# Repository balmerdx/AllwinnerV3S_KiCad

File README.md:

# Balmer Allwinner V3S KICAD scematic & pcb

Allwinner V3S - это пожалуй один из наиболее дешёвых system on chip для embedded linux.

Перечислю его ключевые особенности.
* встроенные 64 мегабайта DRAM
* RGB интерфейс для подключения дисплея
* встроенный PNY для Ethernet 100 Mbit
* USB 2.0 OTG
* встроенный DAC и усилитель для наушников

Это позволяет сделать достаточно дешёвый одноплатник.

Обратите внимание!!!! Плата разведена для Step-Down на EA3036. Микросхема EA3036C имеет несколько другой pinout. К сожалению мне прислали EA3036C, и поэтому на плате есть некрасивое место с её вкорячиванием.

Плата разведена под дисплей с 800x480 с capacitive touch (G05012AG02A1, G050AGZ085A1).

То-же, самое но с корпусом.

### Сравним с Lichee PI

По размеру мой вариант несколько больше. Но за счёт расположенных разъёмов конечный вариант будет явно компактнее. Разводка Lichee PI мне нравится как пример максимально плотного монтажа. Для отладки это нормально. Но в реальной жизни непонятно, что делать с этими случайным образом раскиданными разъёмами.

### Информация
* [Схема в pdf формате](info/balmer_allwinner_v3s_v2.pdf)
* [Информация, как собирать linux](info/Buildroot_AllwinnerV3S.pdf)

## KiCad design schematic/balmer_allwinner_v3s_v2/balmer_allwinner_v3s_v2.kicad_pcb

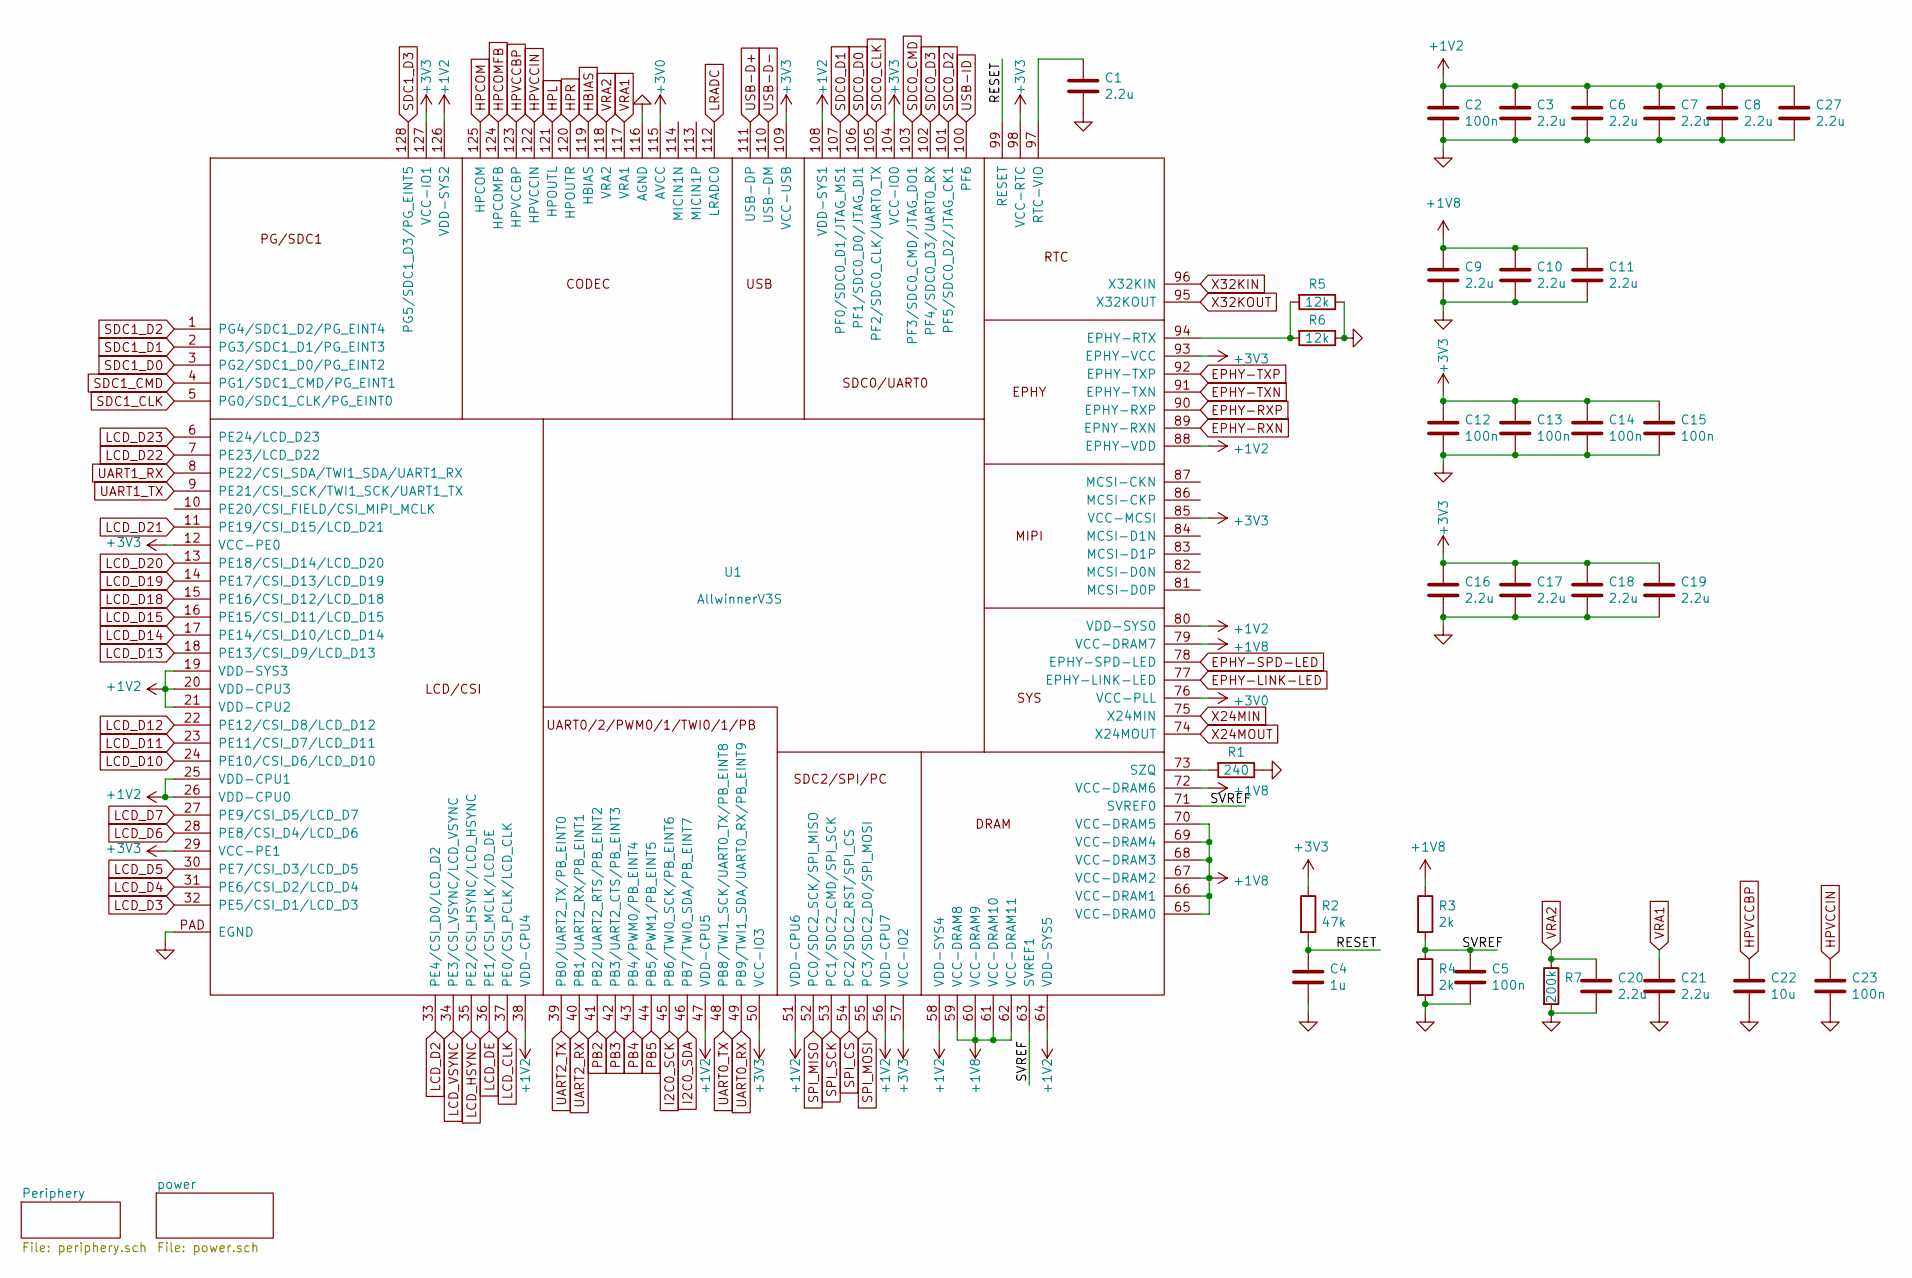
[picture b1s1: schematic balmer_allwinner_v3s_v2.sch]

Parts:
C1, C3, C6, C7, C8, C9, C10, C11, C16, C17, C18, C19, C20, C21, C27: 2.2u; C_0805_2012Metric
C2, C5, C12, C13, C14, C15, C23: 100n; C_0603_1608Metric
C4: 1u; C_0603_1608Metric
C22: 10u; C_0805_2012Metric
R1: 240; R_0603_1608Metric
R2: 47k; R_0603_1608Metric
R3, R4: 2k; R_0603_1608Metric
R5, R6: 12k; R_0603_1608Metric
R7: 200k; R_0603_1608Metric
U1: AllwinnerV3S; eLQFP-128_14x14mm_P0.4mm

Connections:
+1V2: C2.1, C3.1, C6.1, C7.1, C8.1, C27.1, U1.19 (VDD-SYS3), U1.20 (VDD-CPU3), U1.21 (VDD-CPU2), U1.25 (VDD-CPU1), U1.26 (VDD-CPU0), U1.38 (VDD-CPU4), U1.47 (VDD-CPU5), U1.51 (VDD-CPU6), U1.56 (VDD-CPU7), U1.58 (VDD-SYS4), U1.64 (VDD-SYS5), U1.80 (VDD-SYS0), U1.88 (EPHY-VDD), U1.108 (VDD-SYS1), U1.126 (VDD-SYS2); also elsewhere on the board
+1V8: C9.1, C10.1, C11.1, R3.1, U1.59 (VCC-DRAM8), U1.60 (VCC-DRAM9), U1.61 (VCC-DRAM10), U1.62 (VCC-DRAM11), U1.65 (VCC-DRAM0), U1.66 (VCC-DRAM1), U1.67 (VCC-DRAM2), U1.68 (VCC-DRAM3), U1.69 (VCC-DRAM4), U1.70 (VCC-DRAM5), U1.72 (VCC-DRAM6), U1.79 (VCC-DRAM7); also elsewhere on the board
+3V0: U1.76 (VCC-PLL), U1.115 (AVCC); also elsewhere on the board
+3V3: C12.1, C13.1, C14.1, C15.1, C16.1, C17.1, C18.1, C19.1, R2.1, U1.12 (VCC-PE0), U1.29 (VCC-PE1), U1.50 (VCC-IO3), U1.57 (VCC-IO2), U1.85 (VCC-MCSI), U1.93 (EPHY-VCC), U1.98 (VCC-RTC), U1.104 (VCC-IO0), U1.109 (VCC-USB), U1.127 (VCC-IO1); also elsewhere on the board
/RESET: C4.1, R2.2, U1.99 (RESET)
/SVREF: C5.1, R3.2, R4.1, U1.63 (SVREF1), U1.71 (SVREF0)
EPHY-LINK-LED: U1.77 (EPHY-LINK-LED); also elsewhere on the board
EPHY-RXN: U1.89 (EPNY-RXN); also elsewhere on the board
EPHY-RXP: U1.90 (EPHY-RXP); also elsewhere on the board
EPHY-SPD-LED: U1.78 (EPHY-SPD-LED); also elsewhere on the board
EPHY-TXN: U1.91 (EPHY-TXN); also elsewhere on the board
EPHY-TXP: U1.92 (EPHY-TXP); also elsewhere on the board
GND: C1.2, C2.2, C3.2, C4.2, C5.2, C6.2, C7.2, C8.2, C9.2, C10.2, C11.2, C12.2, C13.2, C14.2, C15.2, C16.2, C17.2, C18.2, C19.2, C20.2, C21.2, C22.2, C23.2, C27.2, R1.1, R4.2, R5.1, R6.1, R7.2, U1.116 (AGND), U1.PAD (EGND); also elsewhere on the board
HBIAS: U1.119 (HBIAS); also elsewhere on the board
HPCOM: U1.125 (HPCOM); also elsewhere on the board
HPCOMFB: U1.124 (HPCOMFB); also elsewhere on the board
HPL: U1.121 (HPOUTL); also elsewhere on the board
HPR: U1.120 (HPOUTR); also elsewhere on the board
HPVCCBP: C22.1, U1.123 (HPVCCBP)
HPVCCIN: C23.1, U1.122 (HPVCCIN)
I2C0_SCK: U1.45 (PB6/TWI0_SCK/PB_EINT6); also elsewhere on the board
I2C0_SDA: U1.46 (PB7/TWI0_SDA/PB_EINT7); also elsewhere on the board
LCD_CLK: U1.37 (PE0/CSI_PCLK/LCD_CLK); also elsewhere on the board
LCD_D2: U1.33 (PE4/CSI_D0/LCD_D2); also elsewhere on the board
LCD_D3: U1.32 (PE5/CSI_D1/LCD_D3); also elsewhere on the board
LCD_D4: U1.31 (PE6/CSI_D2/LCD_D4); also elsewhere on the board
LCD_D5: U1.30 (PE7/CSI_D3/LCD_D5); also elsewhere on the board
LCD_D6: U1.28 (PE8/CSI_D4/LCD_D6); also elsewhere on the board
LCD_D7: U1.27 (PE9/CSI_D5/LCD_D7); also elsewhere on the board
LCD_D10: U1.24 (PE10/CSI_D6/LCD_D10); also elsewhere on the board
LCD_D11: U1.23 (PE11/CSI_D7/LCD_D11); also elsewhere on the board
LCD_D12: U1.22 (PE12/CSI_D8/LCD_D12); also elsewhere on the board
LCD_D13: U1.18 (PE13/CSI_D9/LCD_D13); also elsewhere on the board
LCD_D14: U1.17 (PE14/CSI_D10/LCD_D14); also elsewhere on the board
LCD_D15: U1.16 (PE15/CSI_D11/LCD_D15); also elsewhere on the board
LCD_D18: U1.15 (PE16/CSI_D12/LCD_D18); also elsewhere on the board
LCD_D19: U1.14 (PE17/CSI_D13/LCD_D19); also elsewhere on the board
LCD_D20: U1.13 (PE18/CSI_D14/LCD_D20); also elsewhere on the board
LCD_D21: U1.11 (PE19/CSI_D15/LCD_D21); also elsewhere on the board
LCD_D22: U1.7 (PE23/LCD_D22); also elsewhere on the board
LCD_D23: U1.6 (PE24/LCD_D23); also elsewhere on the board
LCD_DE: U1.36 (PE1/CSI_MCLK/LCD_DE); also elsewhere on the board
LCD_HSYNC: U1.35 (PE2/CSI_HSYNC/LCD_HSYNC); also elsewhere on the board
LCD_VSYNC: U1.34 (PE3/CSI_VSYNC/LCD_VSYNC); also elsewhere on the board
LRADC: U1.112 (LRADC0); also elsewhere on the board
unnamed: C1.1, U1.97 (RTC-VIO)
unnamed: R1.2, U1.73 (SZQ)
unnamed: R5.2, R6.2, U1.94 (EPHY-RTX)
PB2: U1.41 (PB2/UART2_RTS/PB_EINT2); also elsewhere on the board
PB3: U1.42 (PB3/UART2_CTS/PB_EINT3); also elsewhere on the board
PB4: U1.43 (PB4/PWM0/PB_EINT4); also elsewhere on the board
PB5: U1.44 (PB5/PWM1/PB_EINT5); also elsewhere on the board
SDC0_CLK: U1.105 (PF2/SDC0_CLK/UART0_TX); also elsewhere on the board
SDC0_CMD: U1.103 (PF3/SDC0_CMD/JTAG_DO1); also elsewhere on the board
SDC0_D0: U1.106 (PF1/SDC0_D0/JTAG_DI1); also elsewhere on the board
SDC0_D1: U1.107 (PF0/SDC0_D1/JTAG_MS1); also elsewhere on the board
SDC0_D2: U1.101 (PF5/SDC0_D2/JTAG_CK1); also elsewhere on the board
SDC0_D3: U1.102 (PF4/SDC0_D3/UART0_RX); also elsewhere on the board
SDC1_CLK: U1.5 (PG0/SDC1_CLK/PG_EINT0); also elsewhere on the board
SDC1_CMD: U1.4 (PG1/SDC1_CMD/PG_EINT1); also elsewhere on the board
SDC1_D0: U1.3 (PG2/SDC1_D0/PG_EINT2); also elsewhere on the board
SDC1_D1: U1.2 (PG3/SDC1_D1/PG_EINT3); also elsewhere on the board
SDC1_D2: U1.1 (PG4/SDC1_D2/PG_EINT4); also elsewhere on the board
SDC1_D3: U1.128 (PG5/SDC1_D3/PG_EINT5); also elsewhere on the board
SPI_CS: U1.54 (PC2/SDC2_RST/SPI_CS); also elsewhere on the board
SPI_MISO: U1.52 (PC0/SDC2_SCK/SPI_MISO); also elsewhere on the board
SPI_MOSI: U1.55 (PC3/SDC2_D0/SPI_MOSI); also elsewhere on the board
SPI_SCK: U1.53 (PC1/SDC2_CMD/SPI_SCK); also elsewhere on the board
UART0_RX: U1.49 (PB9/TWI1_SDA/UART0_RX/PB_EINT9); also elsewhere on the board
UART0_TX: U1.48 (PB8/TWI1_SCK/UART0_TX/PB_EINT8); also elsewhere on the board
UART1_RX: U1.8 (PE22/CSI_SDA/TWI1_SDA/UART1_RX); also elsewhere on the board
UART1_TX: U1.9 (PE21/CSI_SCK/TWI1_SCK/UART1_TX); also elsewhere on the board
UART2_RX: U1.40 (PB1/UART2_RX/PB_EINT1); also elsewhere on the board
UART2_TX: U1.39 (PB0/UART2_TX/PB_EINT0); also elsewhere on the board
USB-D+: U1.111 (USB-DP); also elsewhere on the board
USB-D-: U1.110 (USB-DM); also elsewhere on the board
USB-ID: U1.100 (PF6); also elsewhere on the board
VRA1: C21.1, U1.117 (VRA1)
VRA2: C20.1, R7.1, U1.118 (VRA2)
X24MIN: U1.75 (X24MIN); also elsewhere on the board
X24MOUT: U1.74 (X24MOUT); also elsewhere on the board
X32KIN: U1.96 (X32KIN); also elsewhere on the board
X32KOUT: U1.95 (X32KOUT); also elsewhere on the board

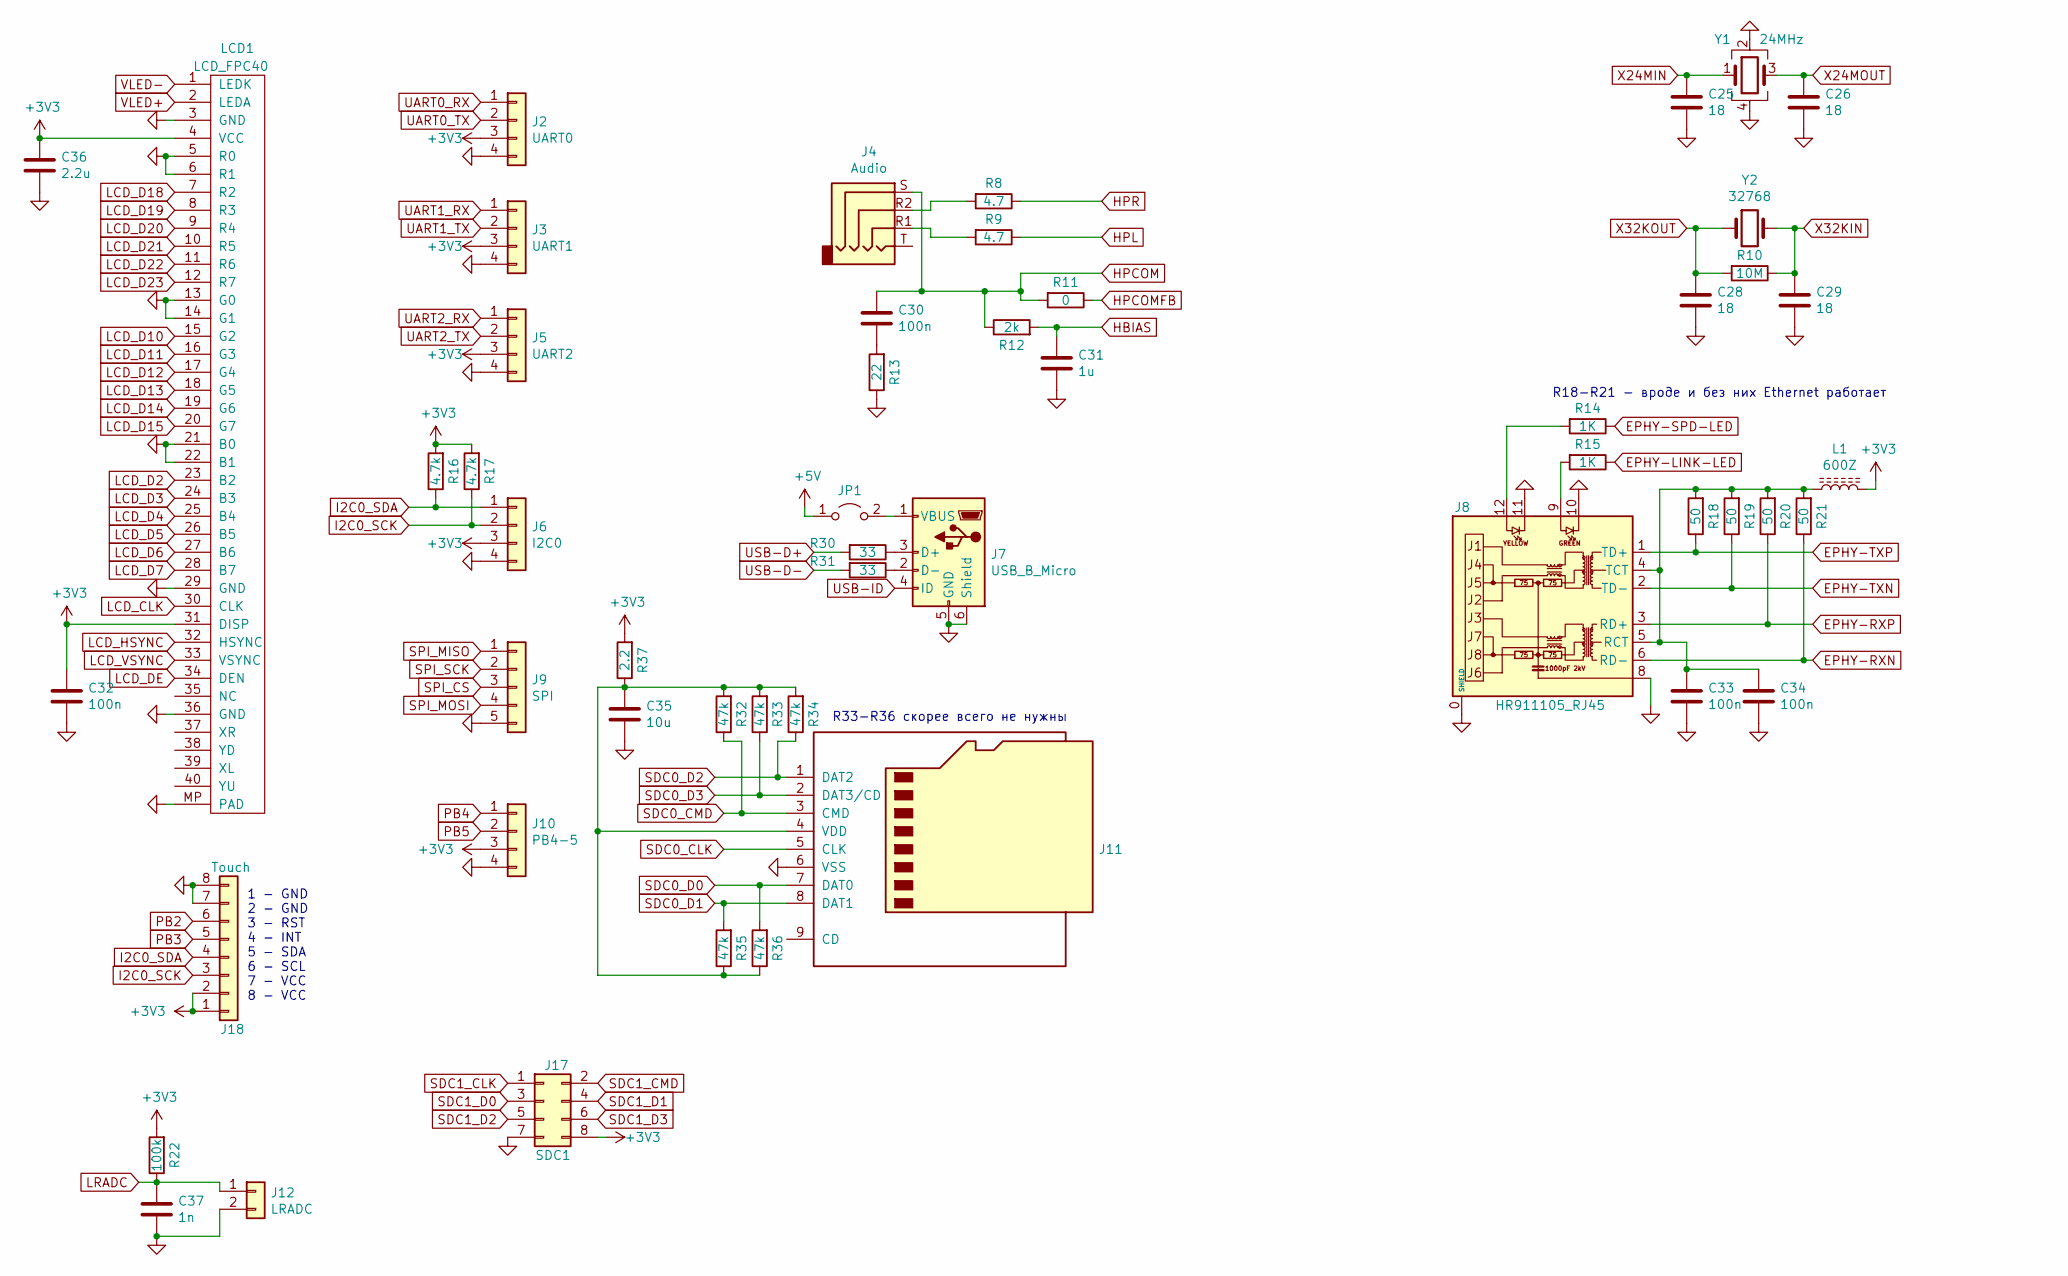
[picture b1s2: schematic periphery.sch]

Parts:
C25, C26, C28, C29: 18; C_0603_1608Metric
C30, C32, C33, C34: 100n; C_0603_1608Metric
C31: 1u; C_0603_1608Metric
C35: 10u; C_1206_3216Metric
C36: 2.2u; C_0805_2012Metric
C37: 1n; C_0603_1608Metric
J2: UART0; PinSocket_1x04_P1.27mm_Vertical
J3: UART1; PinSocket_1x04_P1.27mm_Vertical
J4: Audio; Jack_3.5mm_PJ320D_Horizontal
J5: UART2; PinSocket_1x04_P1.27mm_Vertical
J6: I2C0; PinSocket_1x04_P1.27mm_Vertical
J7: USB_B_Micro; USB_Micro-B_Molex-105017-0001
J8: HR911105_RJ45
J9: SPI; PinSocket_1x05_P1.27mm_Vertical
J10: PB4-5; PinSocket_1x04_P1.27mm_Vertical
J11: Micro_SD_Card_Ebay; Conn_uSDcard
J12: LRADC; PinSocket_1x02_P1.27mm_Vertical
J17: SDC1; PinHeader_2x04_P2.54mm_Vertical
J18: Touch; Hirose_FH12-8S-0.5SH_1x08-1MP_P0.50mm_Horizontal
JP1: Jumper_2_Open; PinHeader_1x02_P2.00mm_Vertical
L1: 600Z; L_1206_3216Metric
LCD1: LCD_FPC40; Hirose_FH12-40S-0.5SH_1x40-1MP_P0.50mm_Horizontal
R8, R9: 4.7; R_0603_1608Metric
R10: 10M; R_0805_2012Metric
R11: 0; R_0603_1608Metric
R12: 2k; R_0603_1608Metric
R13: 22; R_0603_1608Metric
R14, R15: 1K; R_0603_1608Metric
R16, R17: 4.7k; R_0603_1608Metric
R18, R19, R20, R21: 50; R_0603_1608Metric
R22: 100k; R_0603_1608Metric
R30, R31: 33; R_0603_1608Metric
R32, R33, R34, R35, R36: 47k; R_0603_1608Metric
R37: 2.2; R_0805_2012Metric
Y1: 24MHz; Crystal_SMD_3225-4Pin_3.2x2.5mm
Y2: 32768; Crystal_C26-LF_D2.1mm_L6.5mm_Horizontal

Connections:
+3V3: C32.1, C36.1, J2.3, J3.3, J5.3, J6.3, J10.3, J17.8, J18.1, J18.2, L1.2, LCD1.4 (VCC), LCD1.31 (DISP), R16.2, R17.2, R22.2, R37.2; also elsewhere on the board
+5V: JP1.1 (A); also elsewhere on the board
EPHY-LINK-LED: R15.1; also elsewhere on the board
EPHY-RXN: J8.6 (RD-), R21.1; also elsewhere on the board
EPHY-RXP: J8.3 (RD+), R20.1; also elsewhere on the board
EPHY-SPD-LED: R14.1; also elsewhere on the board
EPHY-TXN: J8.2 (TD-), R19.1; also elsewhere on the board
EPHY-TXP: J8.1 (TD+), R18.1; also elsewhere on the board
GND: C25.2, C26.2, C28.2, C29.2, C31.2, C32.2, C33.2, C34.2, C35.2, C36.2, C37.2, J2.4, J3.4, J5.4, J6.4, J7.5 (GND), J7.6 (Shield), J8.0 (SHIELD), J8.8, J8.10, J8.11, J9.5, J10.4, J11.6 (VSS), J12.2, J17.7, J18.7, J18.8, LCD1.3 (GND), LCD1.5 (R0), LCD1.6 (R1), LCD1.13 (G0), LCD1.14 (G1), LCD1.21 (B0), LCD1.22 (B1), LCD1.29 (GND), LCD1.36 (GND), LCD1.MP (PAD), R13.1, Y1.2, Y1.4; also elsewhere on the board
HBIAS: C31.1, R12.2; also elsewhere on the board
HPCOM: C30.1, J4.S, R11.2, R12.1; also elsewhere on the board
HPCOMFB: R11.1; also elsewhere on the board
HPL: R9.1; also elsewhere on the board
HPR: R8.1; also elsewhere on the board
I2C0_SCK: J6.2, J18.3, R17.1; also elsewhere on the board
I2C0_SDA: J6.1, J18.4, R16.1; also elsewhere on the board
LCD_CLK: LCD1.30 (CLK); also elsewhere on the board
LCD_D2: LCD1.23 (B2); also elsewhere on the board
LCD_D3: LCD1.24 (B3); also elsewhere on the board
LCD_D4: LCD1.25 (B4); also elsewhere on the board
LCD_D5: LCD1.26 (B5); also elsewhere on the board
LCD_D6: LCD1.27 (B6); also elsewhere on the board
LCD_D7: LCD1.28 (B7); also elsewhere on the board
LCD_D10: LCD1.15 (G2); also elsewhere on the board
LCD_D11: LCD1.16 (G3); also elsewhere on the board
LCD_D12: LCD1.17 (G4); also elsewhere on the board
LCD_D13: LCD1.18 (G5); also elsewhere on the board
LCD_D14: LCD1.19 (G6); also elsewhere on the board
LCD_D15: LCD1.20 (G7); also elsewhere on the board
LCD_D18: LCD1.7 (R2); also elsewhere on the board
LCD_D19: LCD1.8 (R3); also elsewhere on the board
LCD_D20: LCD1.9 (R4); also elsewhere on the board
LCD_D21: LCD1.10 (R5); also elsewhere on the board
LCD_D22: LCD1.11 (R6); also elsewhere on the board
LCD_D23: LCD1.12 (R7); also elsewhere on the board
LCD_DE: LCD1.34 (DEN); also elsewhere on the board
LCD_HSYNC: LCD1.32 (HSYNC); also elsewhere on the board
LCD_VSYNC: LCD1.33 (VSYNC); also elsewhere on the board
LRADC: C37.1, J12.1, R22.1; also elsewhere on the board
unnamed: C30.2, R13.2
unnamed: C33.1, C34.1, J8.4 (TCT), J8.5 (RCT), L1.1, R18.2, R19.2, R20.2, R21.2
unnamed: C35.1, J11.4 (VDD), R32.2, R33.2, R34.2, R35.1, R36.1, R37.1
unnamed: J4.R1, R9.2
unnamed: J4.R2, R8.2
unnamed: J7.1 (VBUS), JP1.2 (B)
unnamed: J7.2 (D-), R31.1
unnamed: J7.3 (D+), R30.1
unnamed: J8.9, R15.2
unnamed: J8.12, R14.2
PB2: J18.6; also elsewhere on the board
PB3: J18.5; also elsewhere on the board
PB4: J10.1; also elsewhere on the board
PB5: J10.2; also elsewhere on the board
SDC0_CLK: J11.5 (CLK); also elsewhere on the board
SDC0_CMD: J11.3 (CMD), R32.1; also elsewhere on the board
SDC0_D0: J11.7 (DAT0), R36.2; also elsewhere on the board
SDC0_D1: J11.8 (DAT1), R35.2; also elsewhere on the board
SDC0_D2: J11.1 (DAT2), R34.1; also elsewhere on the board
SDC0_D3: J11.2 (DAT3/CD), R33.1; also elsewhere on the board
SDC1_CLK: J17.1; also elsewhere on the board
SDC1_CMD: J17.2; also elsewhere on the board
SDC1_D0: J17.3; also elsewhere on the board
SDC1_D1: J17.4; also elsewhere on the board
SDC1_D2: J17.5; also elsewhere on the board
SDC1_D3: J17.6; also elsewhere on the board
SPI_CS: J9.3; also elsewhere on the board
SPI_MISO: J9.1; also elsewhere on the board
SPI_MOSI: J9.4; also elsewhere on the board
SPI_SCK: J9.2; also elsewhere on the board
UART0_RX: J2.1; also elsewhere on the board
UART0_TX: J2.2; also elsewhere on the board
UART1_RX: J3.1; also elsewhere on the board
UART1_TX: J3.2; also elsewhere on the board
UART2_RX: J5.1; also elsewhere on the board
UART2_TX: J5.2; also elsewhere on the board
USB-D+: R30.2; also elsewhere on the board
USB-D-: R31.2; also elsewhere on the board
USB-ID: J7.4 (ID); also elsewhere on the board
VLED+: LCD1.2 (LEDA); also elsewhere on the board
VLED-: LCD1.1 (LEDK); also elsewhere on the board
X24MIN: C25.1, Y1.1; also elsewhere on the board
X24MOUT: C26.1, Y1.3; also elsewhere on the board
X32KIN: C29.1, R10.1, Y2.2; also elsewhere on the board
X32KOUT: C28.1, R10.2, Y2.1; also elsewhere on the board

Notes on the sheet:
1 - GND 2 - GND 3 - RST 4 - INT 5 - SDA 6 - SCL 7 - VCC 8 - VCC
R18-R21 - вроде и без них Ethernet работает
R33-R36 скорее всего не нужны

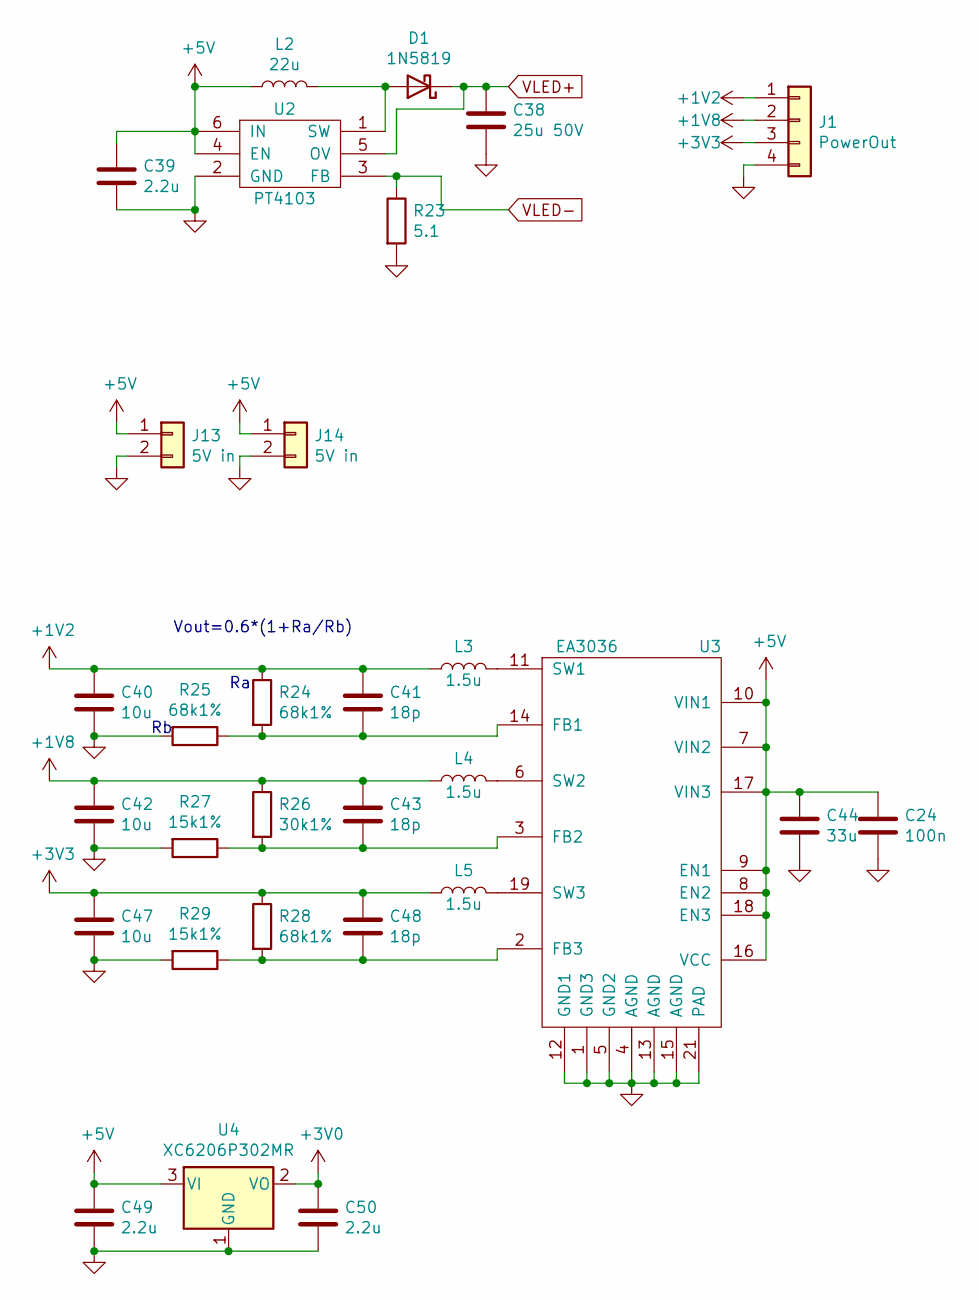
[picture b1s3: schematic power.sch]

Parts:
C24: 100n; C_0603_1608Metric
C38: 25u 50V; C_1206_3216Metric
C39, C49, C50: 2.2u; C_0805_2012Metric
C40, C42, C47: 10u; C_0805_2012Metric
C41, C43, C48: 18p; C_0603_1608Metric
C44: 33u; C_1206_3216Metric
D1: 1N5819; D_SOD-123
J1: PowerOut; PinSocket_1x04_P1.27mm_Vertical
J13: 5V in; PinSocket_1x02_P1.27mm_Vertical
J14: 5V in; PinSocket_1x02_P2.54mm_Vertical
L2: 22u; L_Taiyo-Yuden_NR-60xx
L3, L4, L5: 1.5u; L_TDK_SLF6045
R23: 5.1; R_0603_1608Metric
R24, R25, R28: 68k1%; R_0603_1608Metric
R26: 30k1%; R_0603_1608Metric
R27, R29: 15k1%; R_0603_1608Metric
U2: PT4103; SOT-23-6
U3: EA3036; QFN-20-1EP_3x3mm_P0.4mm_EP1.65x1.65mm_ThermalVias
U4: XC6206P302MR; SOT-23

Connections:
+1V2: C40.1, C41.1, J1.1, L3.1, R24.1; also elsewhere on the board
+1V8: C42.1, C43.1, J1.2, L4.1, R26.1; also elsewhere on the board
+3V0: C50.1, U4.2 (VO); also elsewhere on the board
+3V3: C47.1, C48.1, J1.3, L5.1, R28.1; also elsewhere on the board
+5V: C24.1, C39.1, C44.1, C49.1, J13.1, J14.1, L2.1, U2.4 (EN), U2.6 (IN), U3.7 (VIN2), U3.8 (EN2), U3.9 (EN1), U3.10 (VIN1), U3.16 (VCC), U3.17 (VIN3), U3.18 (EN3), U4.3 (VI); also elsewhere on the board
GND: C24.2, C38.2, C39.2, C40.2, C42.2, C44.2, C47.2, C49.2, C50.2, J1.4, J13.2, J14.2, R23.2, R25.2, R27.2, R29.2, U2.2 (GND), U3.1 (GND3), U3.4 (AGND), U3.5 (GND2), U3.12 (GND1), U3.13 (AGND), U3.15 (AGND), U3.21 (PAD), U4.1 (GND); also elsewhere on the board
unnamed: C41.2, R24.2, R25.1, U3.14 (FB1)
unnamed: C43.2, R26.2, R27.1, U3.3 (FB2)
unnamed: C48.2, R28.2, R29.1, U3.2 (FB3)
unnamed: D1.2 (A), L2.2, U2.1 (SW)
unnamed: L3.2, U3.11 (SW1)
unnamed: L4.2, U3.6 (SW2)
unnamed: L5.2, U3.19 (SW3)
VLED+: C38.1, D1.1 (K), U2.5 (OV); also elsewhere on the board
VLED-: R23.1, U2.3 (FB); also elsewhere on the board

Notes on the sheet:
Vout=0.6*(1+Ra/Rb)

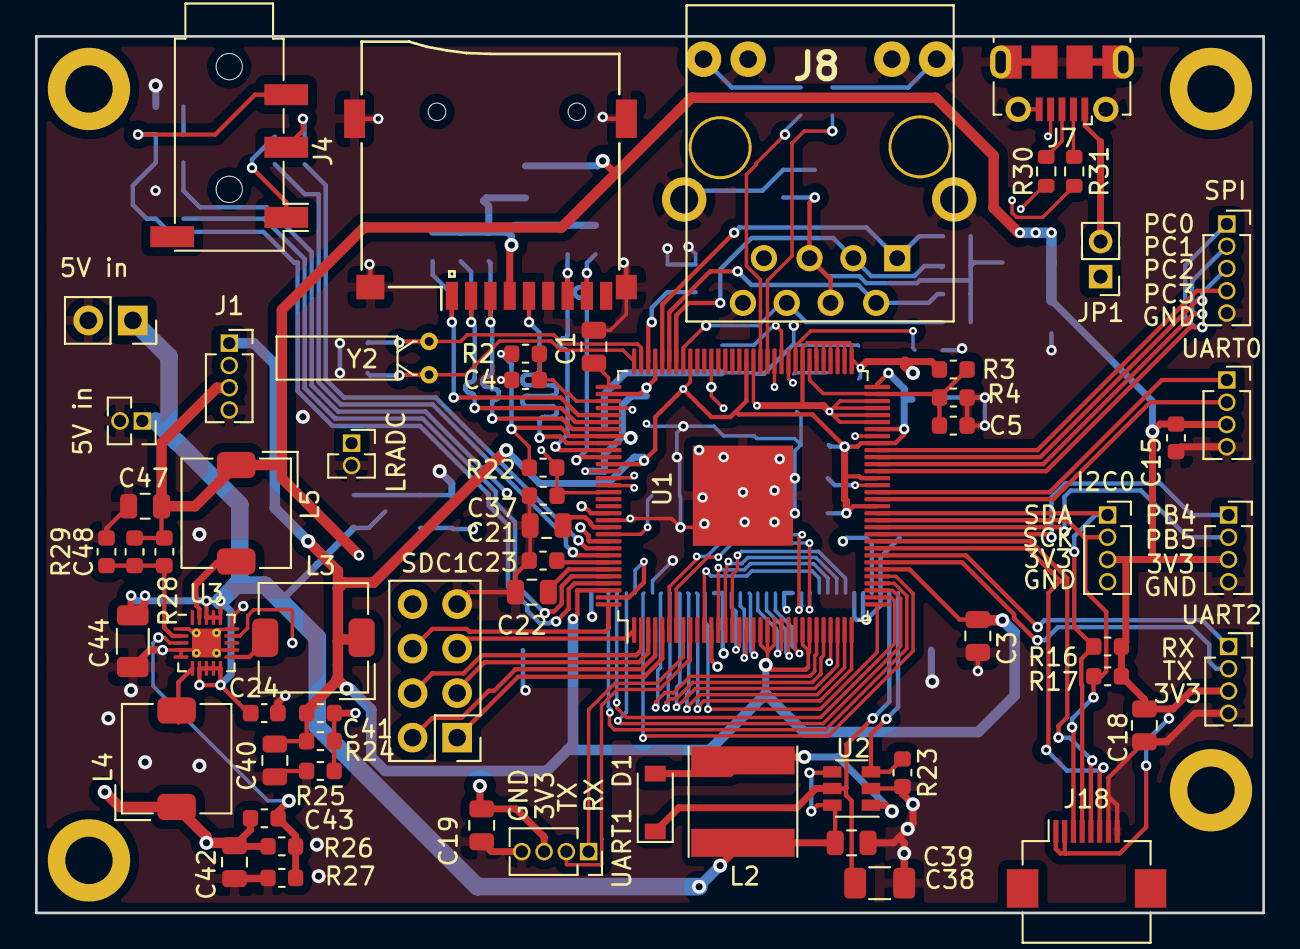
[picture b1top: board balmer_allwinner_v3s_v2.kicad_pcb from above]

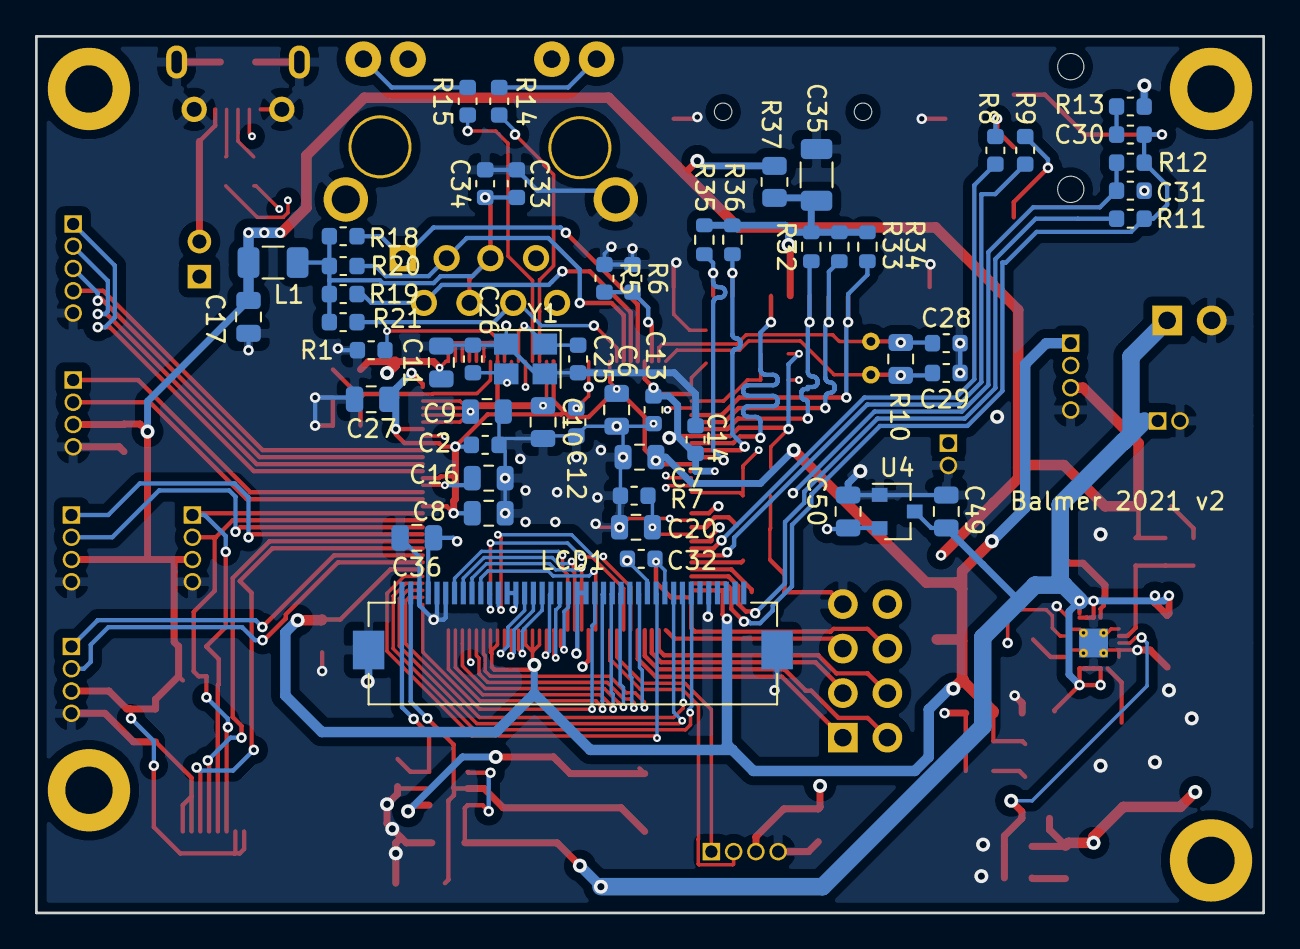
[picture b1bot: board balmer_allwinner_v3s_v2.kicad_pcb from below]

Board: 4 copper layers, 70.0 x 50.0 mm, 115 parts (53 on the bottom side), 103 nets.

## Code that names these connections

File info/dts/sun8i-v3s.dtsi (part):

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			#interrupt-cells = <3>;

			i2c0_pins: i2c0 {
				pins = "PB6", "PB7";
				function = "i2c0";
			};

			pwm0_pins: pwm0 {
				pins = "PB4";
				function = "pwm0";
			};

			uart0_pins_a: uart0@0 {
				pins = "PB8", "PB9";
				function = "uart0";
			};

			lcd_rgb666_pins_a: lcd-rgb666-pe {
				pins = "PE0", "PE1", "PE2", "PE3", "PE4", "PE5",
				       "PE6", "PE7", "PE8", "PE9", "PE10", "PE11",
				       "PE12", "PE13", "PE14", "PE15", "PE16", "PE17",
				       "PE18", "PE19", "PE23", "PE24";
				function = "lcd";
			};

			mmc0_pins_a: mmc0@0 {
				pins = "PF0", "PF1", "PF2", "PF3",
				       "PF4", "PF5";
				function = "mmc0";
				drive-strength = <30>;
				bias-pull-up;
			};

			mmc1_pins: mmc1 {
				pins = "PG0", "PG1", "PG2", "PG3",
				       "PG4", "PG5";
				function = "mmc1";
				drive-strength = <30>;
				bias-pull-up;
			};

			spi0_pins: spi0 {
				pins = "PC0", "PC1", "PC2", "PC3";
				function = "spi0";
			};

			//balmer 
			edt_ft5x06_pins: edt_ft5x06_pins@0 {
				pins = "PB0", "PB1";
				function = "gpio_in";
			};
		};
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
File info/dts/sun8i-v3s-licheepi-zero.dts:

/*
 * Copyright (C) 2016 Icenowy Zheng <icenowy@aosc.xyz>
 *
 * This file is dual-licensed: you can use it either under the terms
 * of the GPL or the X11 license, at your option. Note that this dual
 * licensing only applies to this file, and not this project as a
 * whole.
 *
 *  a) This file is free software; you can redistribute it and/or
 *     modify it under the terms of the GNU General Public License as
 *     published by the Free Software Foundation; either version 2 of the
 *     License, or (at your option) any later version.
 *
 *     This file is distributed in the hope that it will be useful,
 *     but WITHOUT ANY WARRANTY; without even the implied warranty of
 *     MERCHANTABILITY or FITNESS FOR A PARTICULAR PURPOSE.  See the
 *     GNU General Public License for more details.
 *
 * Or, alternatively,
 *
 *  b) Permission is hereby granted, free of charge, to any person
 *     obtaining a copy of this software and associated documentation
 *     files (the "Software"), to deal in the Software without
 *     restriction, including without limitation the rights to use,
 *     copy, modify, merge, publish, distribute, sublicense, and/or
 *     sell copies of the Software, and to permit persons to whom the
 *     Software is furnished to do so, subject to the following
 *     conditions:
 *
 *     The above copyright notice and this permission notice shall be
 *     included in all copies or substantial portions of the Software.
 *
 *     THE SOFTWARE IS PROVIDED "AS IS", WITHOUT WARRANTY OF ANY KIND,
 *     EXPRESS OR IMPLIED, INCLUDING BUT NOT LIMITED TO THE WARRANTIES
 *     OF MERCHANTABILITY, FITNESS FOR A PARTICULAR PURPOSE AND
 *     NONINFRINGEMENT. IN NO EVENT SHALL THE AUTHORS OR COPYRIGHT
 *     HOLDERS BE LIABLE FOR ANY CLAIM, DAMAGES OR OTHER LIABILITY,
 *     WHETHER IN AN ACTION OF CONTRACT, TORT OR OTHERWISE, ARISING
 *     FROM, OUT OF OR IN CONNECTION WITH THE SOFTWARE OR THE USE OR
 *     OTHER DEALINGS IN THE SOFTWARE.
 */

/dts-v1/;
#include "sun8i-v3s.dtsi"
#include "sunxi-common-regulators.dtsi"

/ {
	model = "Lichee Pi Zero";
	compatible = "licheepi,licheepi-zero", "allwinner,sun8i-v3s";

	aliases {
		serial0 = &uart0;
	};

	chosen {
		stdout-path = "serial0:115200n8";
	};

	leds {
		compatible = "gpio-leds";

		blue_led {
			label = "licheepi:blue:usr";
			gpios = <&pio 6 1 GPIO_ACTIVE_LOW>; /* PG1 */
		};

		green_led {
			label = "licheepi:green:usr";
			gpios = <&pio 6 0 GPIO_ACTIVE_LOW>; /* PG0 */
			default-state = "on";
		};

		red_led {
			label = "licheepi:red:usr";
			gpios = <&pio 6 2 GPIO_ACTIVE_LOW>; /* PG2 */
		};
	};
};

&ehci0 {
	status = "okay";
};

&mmc0 {
	pinctrl-0 = <&mmc0_pins_a>;
	pinctrl-names = "default";
	broken-cd;
	bus-width = <4>;
	vmmc-supply = <&reg_vcc3v3>;
	status = "okay";
};

/* //balmer disable capacitive touch
&i2c0 {
	status = "okay";

	ns2009: ns2009@48 {
		compatible = "nsiway,ns2009";
		reg = <0x48>;
	};
};
*/

//balmer test touch
&i2c0 {
    status = "okay";

    polytouch: edt-ft5x06@38 {

        compatible = "edt,edt-ft5406";
        reg = <0x38>;
		interrupt-parent = <&pio>;
		interrupts = <1 3 IRQ_TYPE_EDGE_FALLING>; //PB3
		//wake-gpios = <1 0 GPIO_ACTIVE_LOW>; //PB0
		reset-gpios = <&pio 1 2 GPIO_ACTIVE_LOW>; //PB2
		pinctrl-names = "default";
		pinctrl-0 = <&edt_ft5x06_pins>;
    };
};


&ohci0 {
	status = "okay";
};

&uart0 {
	pinctrl-0 = <&uart0_pins_a>;
	pinctrl-names = "default";
	status = "okay";
};

&usb_otg {
	dr_mode = "otg";
	status = "okay";
};

&usbphy {
	usb0_id_det-gpio = <&pio 5 6 GPIO_ACTIVE_HIGH>;
	status = "okay";
};

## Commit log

2021-04-15 - schematic & initial docs
2021-05-08 - кусочек коробочки
2021-05-08 - readme
